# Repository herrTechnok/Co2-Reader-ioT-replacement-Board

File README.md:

# Co2 Reader ioT replacement Board

This is a replacement board for the air quality sensor that was previously used in my school but gets frequently broken.
| Schematic  | PCB | Render |
| ------------- | ------------- | ------------- |
|    |   |  |

### What are the Features?
It fits into the same case and displays air quality using an RGB LED. But it could be used for something else, everything is configuable via HA

The board runs ESPHome and sends data to Home Assistant. It measures temperature, humidity, and CO₂ levels.

### BOM
| Price  | Component | Where? |
| ------------- | ------------- | ------------- |
| 8,99€  |  YIXISI PCB Mount Screw Terminal Block  | Amazon  |
| 3€  | APA106 led  | Aliexpress  |
| 1,69€  | Wemos D1 Mini  | Aliexpress  |
| 2€  | PCB  | JLPCB  |
| 7,81€  | PCB Shipping  | JLPCB  |
| -----  |
| 23,49€  |

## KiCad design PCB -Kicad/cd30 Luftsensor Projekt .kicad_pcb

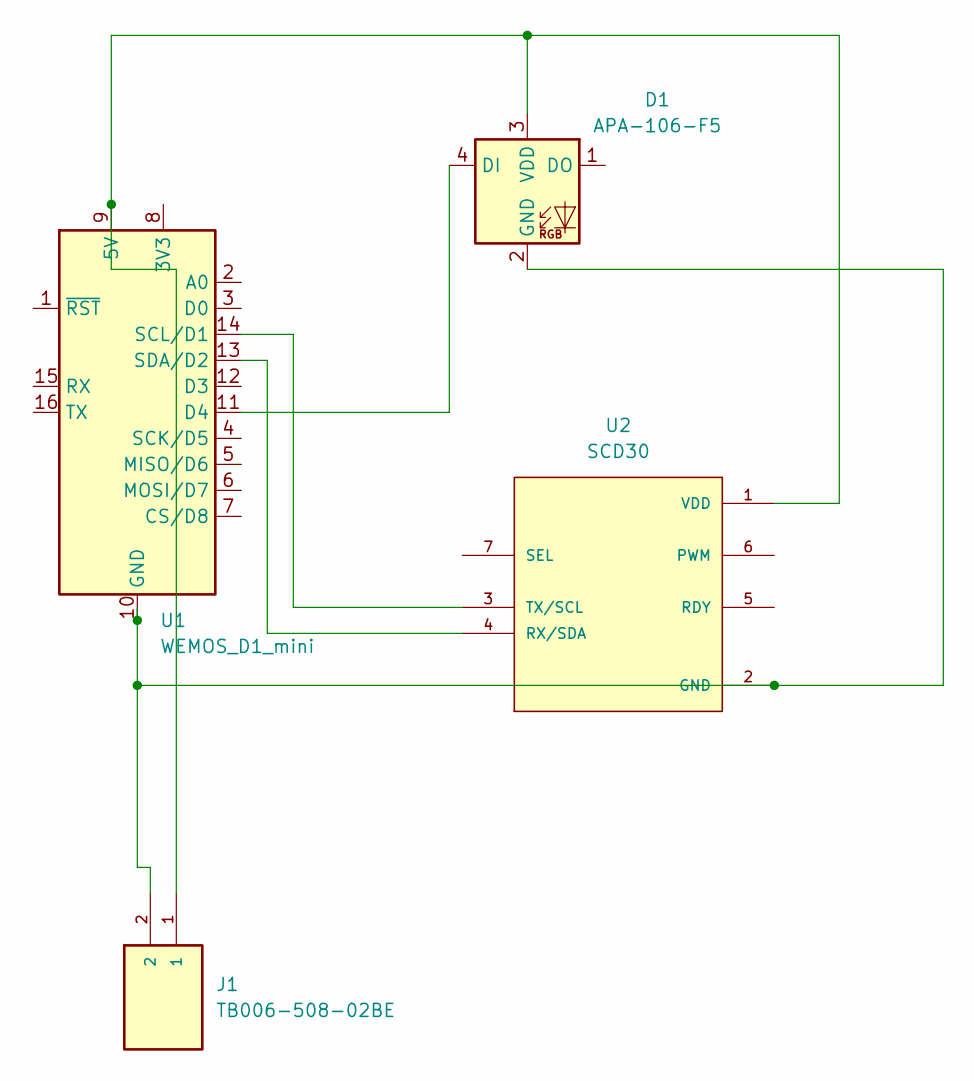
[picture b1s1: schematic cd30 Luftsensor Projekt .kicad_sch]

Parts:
D1: APA-106-F5; LED_D5.0mm-4_RGB
J1: TB006-508-02BE; CUI_TB006-508-02BE
U1: WEMOS_D1_mini; WEMOS_D1_mini_light
U2: SCD30; MODULE_SCD30; PARTREV D1

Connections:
unnamed: D1.4 (DI), U1.11 (D4)
unnamed: D1.2 (GND), J1.2, U1.10 (GND), U2.2 (GND)
unnamed: D1.3 (VDD), J1.1, U1.9 (5V), U2.1 (VDD)
unnamed: U1.14 (SCL/D1), U2.3 (TX/SCL)
unnamed: U1.13 (SDA/D2), U2.4 (RX/SDA)

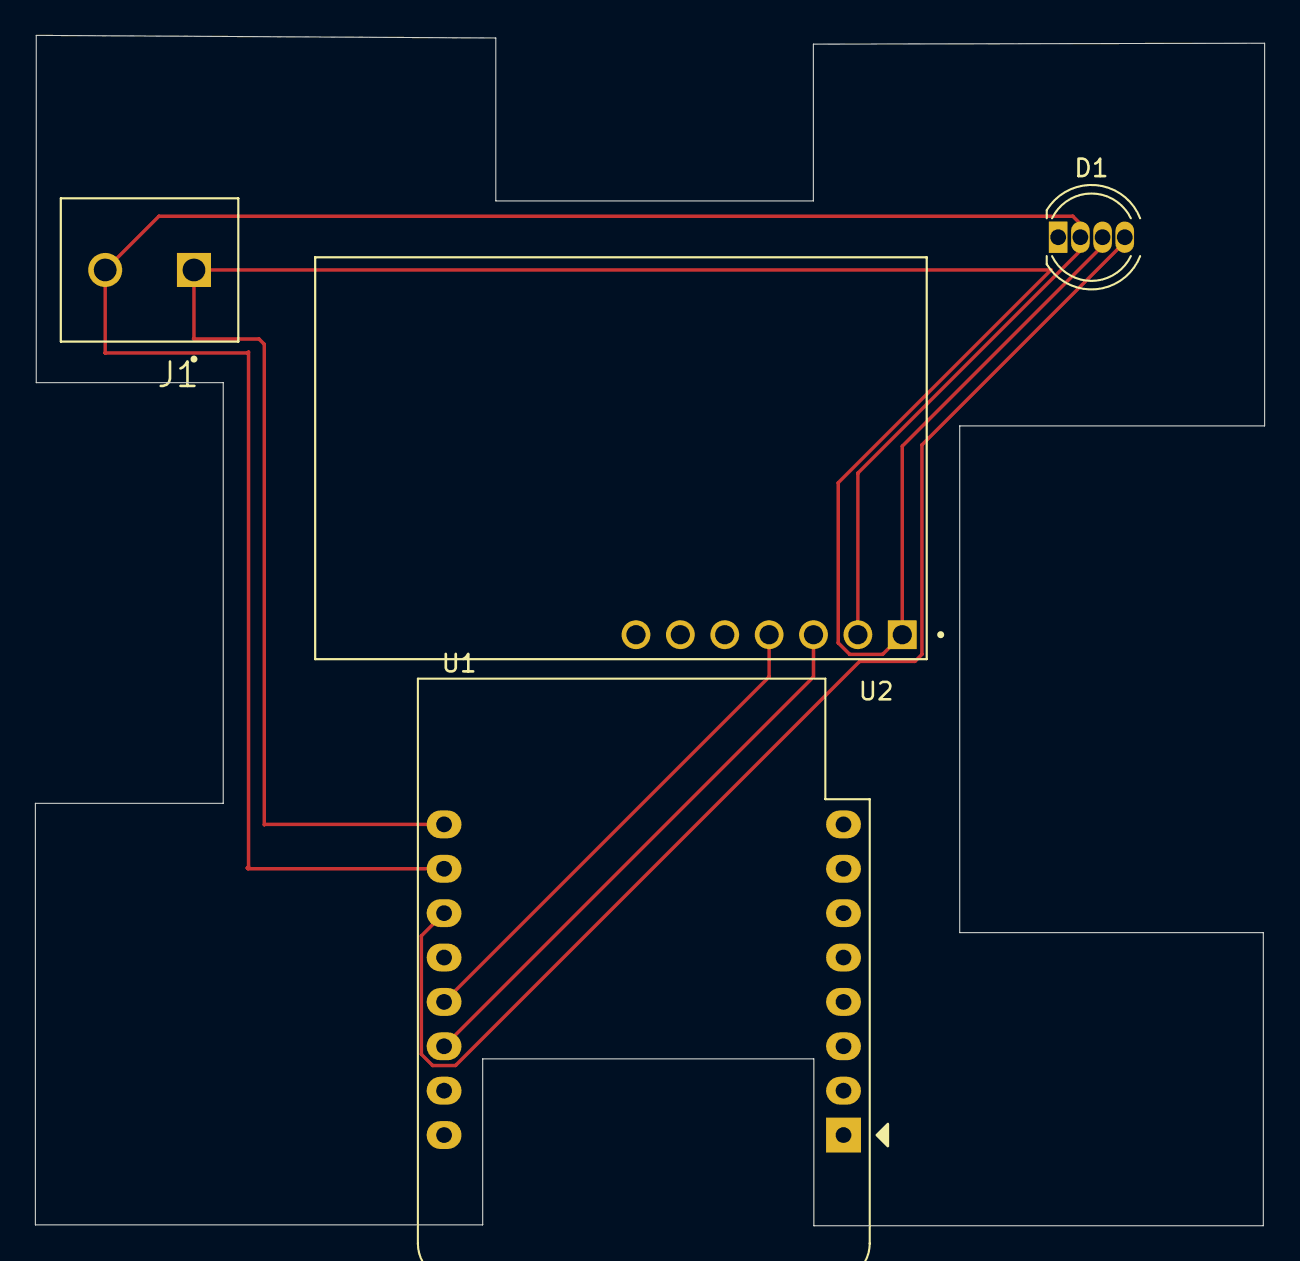
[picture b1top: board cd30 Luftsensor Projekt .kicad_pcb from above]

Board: 2 copper layers, 70.4 x 68.1 mm, 4 parts (0 on the bottom side), 5 nets.

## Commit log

2025-06-18 Upload Files
2025-06-18 Update README.md Add photos
